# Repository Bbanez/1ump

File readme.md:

# Overview #

1ump is a project started with a goal to develope software and hardware tools needed to create fast, simple and reliable communication networks with focus on embedded devices. The advantage of 1ump solution and CLIN communication protocol, that will be developed in the scope of this projects, is that it will be Open Source, easy and cheap to implement.

## Milestones ##

- Design and test CLIN interface.
- Design child interface schematic.
- Design parent interface schematic.
- Design and test prototype boards.
- Push revision 1 boards.
- Write API for Arduino, Mbed, AVR and STM platforms.
- Write desktop application for network monitoring and control.

## Custom communication protocol ##

This project will use custom communication protocol called CLIN Protocol (for short CLIN) that is developed in the scope of this project. The goal of CLIN is to allow simple and easy-to-use communication protocol for connecting virtually infinite number of devices with few hardware wires as possible while allowing fast and reliable data transfer. Since UART is widely used, it is supported by majority of MCUs and it can be easily converted to USB protocol, therefore CLIN is based on it. CLIN uses some software and hardware implementations on top of UART to allow data transfer between devices connected to communication bus (in CLIN network).

## Abstract ##

UART is a simple protocol that uses only 2 wires for communication, one is TX (transmit line) and other is RX (receive line). To establish communication between two devices over UART, TX line of one device is connected to RX line of other and vice versa, as shown in Figure 1. If there is more then 2 devices that need to be connected together, there is only one way to connect them over UART with out introducing additional components and that is daisy-chaining devices as shown in Figure 2. This is not a major problem if 3 to 4 devices are in network, big problem arise when there are even more devices in the network. By using daisy-chain, if the first device needs to communicate with last device in the chain, communication packet first needs to pass thru all devices in between them. This is time consuming and can not be implemented in real-time systems, on top of that all devices in middle of the chain need to have 2 UARTs and handle packets that are not for them.  

_Figure 1 - Connecting 2 devices over UART._

_Figure 2 - Connecting more then 2 devices over UART using daisy-chain configuration._

As it can be concluded, this is not very practical, therefore daisy-chain can not be main solution. I2C and SPI will not be considered because I2C is limited to 127 devices in network and SPI uses to many cables and both of them can not be easily converted into USB protocol.

To connect more then 2 devices over UART, interface needs to be implemented as shown in Figure 3. Interface block is the hardware level block which purpose is to allow all devices connected together to pull down RX line of master device. In this configuration slave-to-slave communication can not be achieved. Communication packet will first be transmitted to master device and then be broadcasted to all slave devices in network. This solution has one major problem, since all slave devices are connected to the same lines, 2 or more slave devices can start transmitting at the same time. This will result in error on the master side because data will not have valid format. For this to be solved 1 more wire is included in network that is called BUSY line as shown in Figure 4. This line is used to check if communication bus is free for transmission. For example, every time before slave device transmit data to master, it will check BUSY line. If the line is free (not set) that means that bus is free and that packet can be transmitted. Before transmitting packet, slave device will set BUSY line telling all other slave devices that bus is not free for transmission. This will not completely remove simultaneous transmission that more devices but it will minimize it to insignificant level. 

_Figure 3 - Basic idea for connecting more then 2 devices over 1 UART. Basic TWCL network._

_Figure 4 - Full TWCL network._

## TWCL Network configurations ##

TWCL communication is based on master/slave relationship between devices. There are 2 types of bus lines, master bus and slave bus. There can be many configuration but the typical configuration is to have one master bus that have one master device and many slave-master devices connected to it, while slave-master devices has there own slave bus. This configuration is shown in Figure 4.

In same slave bus, direct slave-to-slave communication can not be achieved, instead slave will send packet to master and master will redirect it to selected slave. In time sensitive application this packet propagation time needs to be considered and it is based on communication speed and master redirect time. For slave-to-slave communication between to different bus lines, propagation time is even longer and is depending on number of redirects. For example (follow the Figure 4), if SLAVE 11 want to send packet to SLAVE 02, packet will first go to SLAVE1/MASTER, then it will be redirected to MASTER and then it will be redirected to SLAVE 02. In this way packet needs to go thru 2 redirect stages. Packet that is sent by master device is always broadcasted with the address of the device that is sending the packet and address of the device where packet needs to go. This means that all slave devices in the bus will receive packet sent by master but only the device with good packet address will process it. Same is applicable to slave-master bus line.

- Basic network configuration shown in figure 3.
- Full or extended network configuration shown in figure 4.
- Nested network configuration shown in figure 5.
- Combined network.

_Figure 5 - Nested TWCL network configuration._

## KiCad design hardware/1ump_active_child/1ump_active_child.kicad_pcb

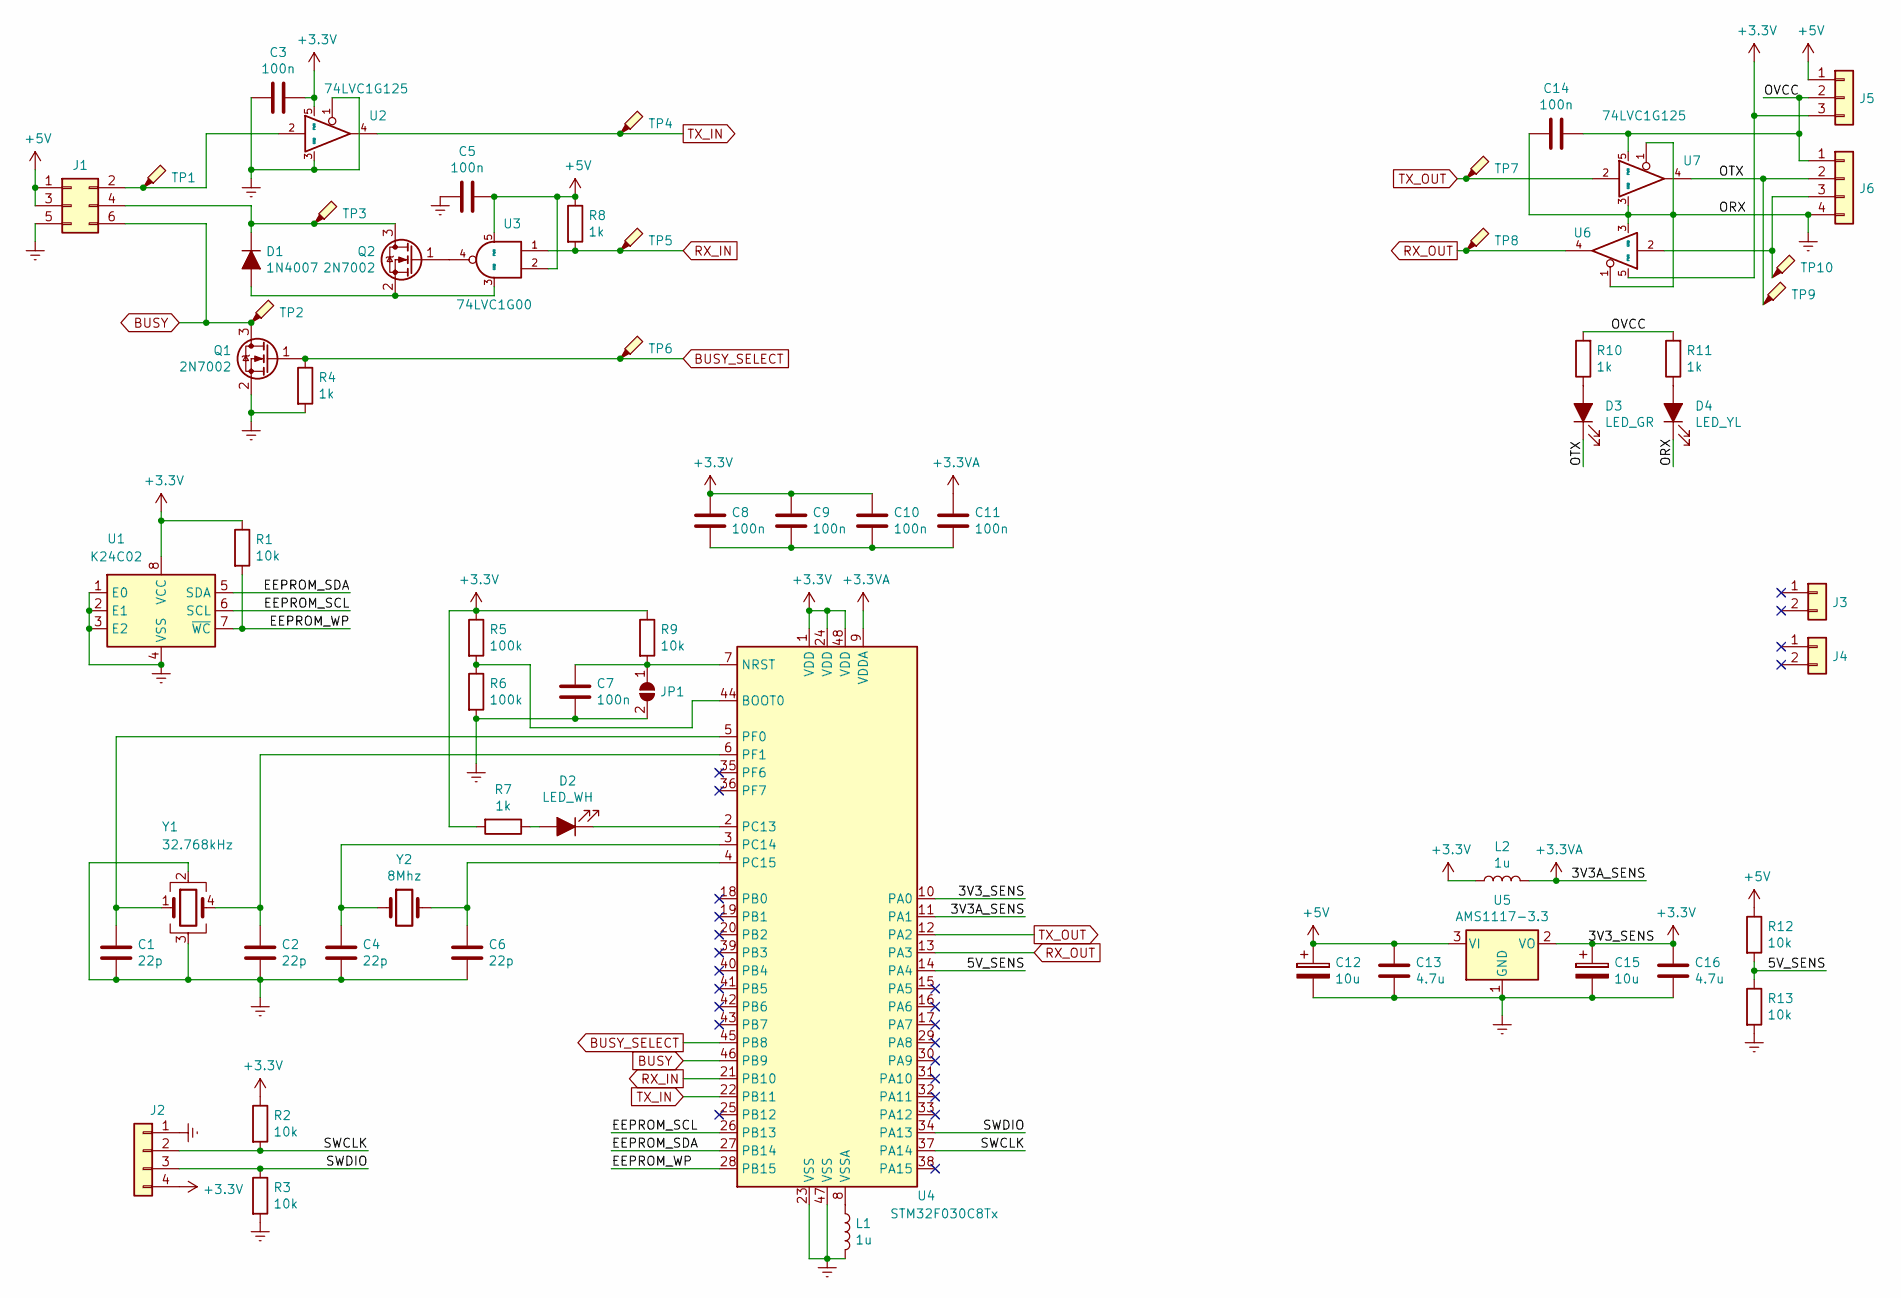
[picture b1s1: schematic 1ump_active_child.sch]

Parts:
C1, C2, C4, C6: 22p; C_0805_2012Metric; LCSC Part C1804
C3, C5, C7, C8, C9, C10, C11, C14: 100n; C_0805_2012Metric; LCSC Part C1804
C12, C15: 10u; CP_Elec_4x4.5
C13, C16: 4.7u; C_0805_2012Metric; LCSC Part C1804
D1: 1N4007; D_0805_2012Metric
D2: LED_WH; LED_0805_2012Metric
D3: LED_GR; LED_0805_2012Metric
D4: LED_YL; LED_0805_2012Metric
J1: Conn_02x03_Odd_Even; PinHeader_2x03_P1.27mm_Vertical
J2, J6: Conn_01x04; JST_PH_S4B-PH-K_1x04_P2.00mm_Horizontal
J3, J4: Conn_01x02; PinHeader_1x02_P1.27mm_Vertical
J5: Conn_01x03; PinHeader_1x03_P2.54mm_Horizontal
JP1: SolderJumper_2_Open; SolderJumper-2_P1.3mm_Open_TrianglePad1.0x1.5mm
L1, L2: 1u; L_0805_2012Metric
Q1, Q2: 2N7002; SOT-23
R1, R2, R3, R9, R12, R13: 10k; R_0805_2012Metric
R4, R7, R8, R10, R11: 1k; R_0805_2012Metric
R5, R6: 100k; R_0805_2012Metric
TP1, TP2, TP3, TP4, TP5, TP6, TP7, TP8, TP9, TP10: TestPoint_Probe; TestPoint_Pad_D1.0mm
U1: K24C02; SOIC-8_3.9x4.9mm_P1.27mm; LCSC Part C83782
U2, U6, U7: 74LVC1G125; SOT-353_SC-70-5
U3: 74LVC1G00; SOT-353_SC-70-5
U4: STM32F030C8Tx; LQFP-48_7x7mm_P0.5mm; LCSC part C23922
U5: AMS1117-3.3; SOT-223-3_TabPin2
Y1: 32.768kHz; Crystal_SMD_SeikoEpson_MC306-4Pin_8.0x3.2mm; LCSC Part C12675
Y2: 8Mhz; Crystal_SMD_HC49-SD; LCSC Part C259041

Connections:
+3.3VA: C11.1, L2.2, U4.9 (VDDA), U4.11 (PA1)
+3V3: C3.2, C8.1, C9.1, C10.1, C15.1, C16.1, J2.4, J5.3, L2.1, R1.1, R2.1, R5.1, R7.2, R9.1, U1.8 (VCC), U2.5 (PWR), U4.1 (VDD), U4.10 (PA0), U4.24 (VDD), U4.48 (VDD), U5.2 (VO), U6.5 (PWR)
+5V: C5.2, C12.1, C13.1, J1.1, J1.3, J5.1, R8.1, R12.1, U3.2, U3.5 (PWR), U5.3 (VI)
/5V_SENS: R12.2, R13.1, U4.14 (PA4)
/EEPROM_SCL: U1.6 (SCL), U4.26 (PB13)
/EEPROM_SDA: U1.5 (SDA), U4.27 (PB14)
/EEPROM_WP: R1.2, U1.7 (~WC), U4.28 (PB15)
/OTX: D3.1 (K), J6.2, TP9.1, U7.4
/OVCC: C14.1, J5.2, J6.1, R10.2, R11.2, U7.5 (PWR)
/SWCLK: J2.2, R2.2, U4.37 (PA14)
/SWDIO: J2.3, R3.1, U4.34 (PA13)
BUSY: J1.6, Q1.3 (D), TP2.1, U4.46 (PB9)
BUSY_SELECT: Q1.1 (G), R4.1, TP6.1, U4.45 (PB8)
Earth: C1.2, C2.2, C3.1, C4.2, C5.1, C6.2, C7.1, C12.2, C13.2, C14.2, C15.2, C16.2, D4.1 (K), J1.5, J2.1, J6.4, JP1.2 (B), L1.2, Q1.2 (S), R3.2, R4.2, R6.2, R13.2, U1.1 (E0), U1.2 (E1), U1.3 (E2), U1.4 (VSS), U2.1, U2.3 (GND), U4.23 (VSS), U4.47 (VSS), U5.1 (GND), U6.1, U6.3 (GND), U7.1, U7.3 (GND), Y1.2, Y1.3
unnamed: C1.1, U4.5 (PF0), Y1.1
unnamed: C2.1, U4.6 (PF1), Y1.4
unnamed: C4.1, U4.3 (PC14), Y2.1
unnamed: C6.1, U4.4 (PC15), Y2.2
unnamed: C7.2, JP1.1 (A), R9.2, U4.7 (NRST)
unnamed: C8.2, C9.2, C10.2, C11.2
unnamed: D1.1 (K), J1.4, Q2.3 (D), TP3.1
unnamed: D1.2 (A), Q2.2 (S), U3.3 (GND)
unnamed: D2.1 (K), U4.2 (PC13)
unnamed: D2.2 (A), R7.1
unnamed: D3.2 (A), R10.1
unnamed: D4.2 (A), R11.1
unnamed: J1.2, TP1.1, U2.2
unnamed: J6.3, TP10.1, U6.2
unnamed: L1.1, U4.8 (VSSA)
unnamed: Q2.1 (G), U3.4
unnamed: R5.2, R6.1, U4.44 (BOOT0)
RX_IN: R8.2, TP5.1, U3.1, U4.21 (PB10)
RX_OUT: TP8.1, U4.13 (PA3), U6.4
TX_IN: TP4.1, U2.4, U4.22 (PB11)
TX_OUT: TP7.1, U4.12 (PA2), U7.2

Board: 2 copper layers, 63 parts (0 on the bottom side), 35 nets, no tracks yet.

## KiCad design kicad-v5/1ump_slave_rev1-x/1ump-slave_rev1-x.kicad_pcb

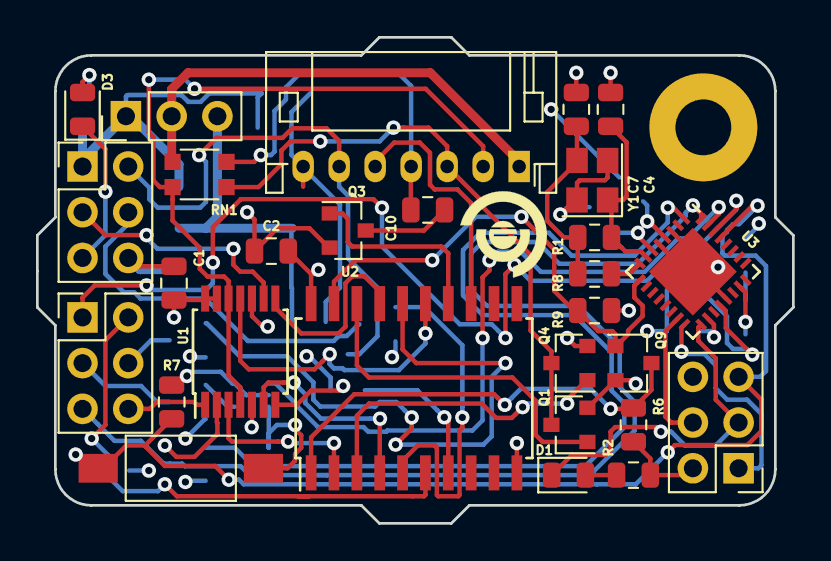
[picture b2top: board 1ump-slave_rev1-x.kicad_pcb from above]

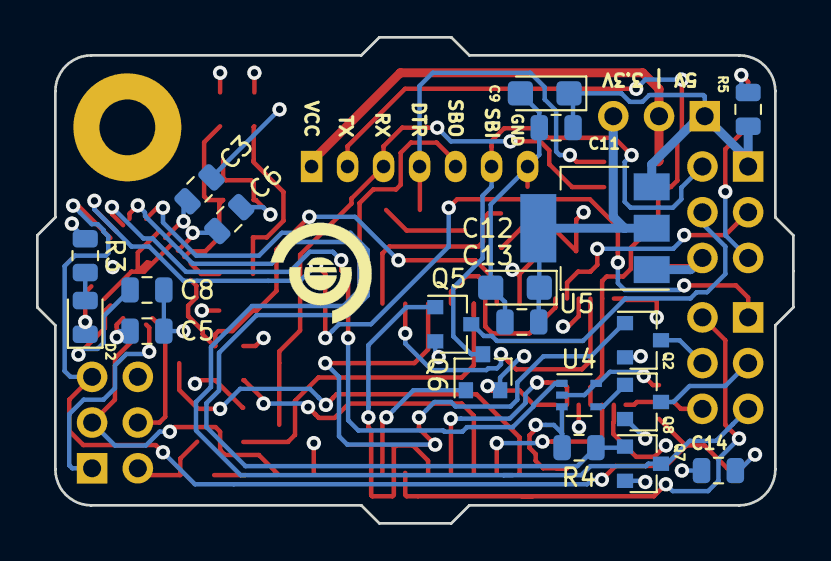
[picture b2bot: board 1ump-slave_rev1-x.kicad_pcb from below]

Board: 4 copper layers, 42.0 x 27.0 mm, 48 parts (20 on the bottom side), 45 nets.

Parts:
C1, C2, C3, C5, C6, C8, C10, C14: 100n; C_0805_2012Metric
C4, C7: 15pF; C_0805_2012Metric
C9, C12: 10u; CP_EIA-3216-12_Kemet-S
C11, C13: 4.7u; C_0805_2012Metric
D1, D2, D3: LED_ALT; LED_0805_2012Metric
J1, J2, J5: Conn_02x03_Odd_Even; PinHeader_2x03_P2.54mm_Vertical
J3: Conn_01x03; PinHeader_1x03_P2.54mm_Vertical
J4: Conn_01x07; JST_PH_S7B-PH-K_1x07_P2.00mm_Horizontal
Q1, Q2, Q3, Q4, Q5, Q6, Q7, Q8, Q9: 2N7002; SOT-23
R1: 1M; R_0805_2012Metric
R2, R3, R5: 1k; R_0805_2012Metric
R4, R6, R7, R9: 10k; R_0805_2012Metric
R8: 0R; R_0805_2012Metric
RN1: 1k; R_Array_Convex_2x1206
SW1: SW_Push; SW_SPST_FSMSM
U1: 74LS00; TSSOP-14_4.4x5mm_P0.65mm
U2: 74HC244; SOIC-20W_7.5x12.8mm_P1.27mm
U3: ATmega328P-MU; QFN-32-1EP_5x5mm_P0.5mm_EP3.45x3.45mm
U4: 74LVC1G00; SOT-353_SC-70-5
U5: AMS1117-3.3; SOT-223-3_TabPin2
Y1: 16MHz_Crystal_GND24; Crystal_SMD_3225-4Pin_3.2x2.5mm

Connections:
+3V3: C12.1, C13.1, J3.3, U5.2
+5V: C1.2, C2.2, C3.1, C5.1, C6.1, C9.1, C11.1, J1.1, J3.1, J5.2, R2.1, R3.1, R5.1, R6.1, R7.1, U1.2, U1.5, U1.10, U1.13, U1.14, U2.20, U3.4, U3.6, U3.18, U4.2, U4.5, U5.3
/BUSY: J2.5, Q7.3, U3.32
/BUSY-SEL: Q7.1, R4.1, U3.1
/CBUS-B: J1.2, J4.6, Q6.3
/CBUS-RX: J1.4, Q5.3
/CBUS-TX: J1.3, U1.9
/CS: Q9.1, R9.1, U2.19, U3.9
/FBUS-DTR: J2.2, U2.6
/FBUS-RX: J2.4, Q2.3
/FBUS-TX: J2.6, U1.1
/MCU-DTR: C10.2, Q3.3
/MCU-RX: J4.3, Q1.3, Q4.3, RN1.3
/MCU-SBO: J4.5, U2.13
/MCU-TX: J4.2, RN1.2, U1.4, U1.12
/MIS: J2.3, Q8.3
/MISO: J5.1, U3.16
/MOS: J2.1, U3.30
/MOSI: J5.4, U3.15
/NCS: Q9.3, R6.2, U2.1
/RST: C14.1, J5.5, R7.2, SW1.1, U3.29
/SCK: D1.1, J5.3, U3.17
/XTAL1: C4.1, R1.2, U3.7, Y1.1
/XTAL2: R8.2, U3.8
Earth: C1.1, C2.1, C3.2, C4.2, C5.2, C6.2, C7.2, C8.2, C9.2, C11.2, C12.2, C13.2, C14.2, D3.1, J1.5, J1.6, J4.7, J5.6, Q1.2, Q2.2, Q3.2, Q4.2, Q5.2, Q6.2, Q7.2, Q8.2, Q9.2, R4.2, R9.2, SW1.2, U1.7, U2.10, U3.3, U3.5, U3.21, U3.33, U4.3, U5.1, Y1.2, Y1.4
unnamed: C7.1, R1.1, R8.1, Y1.3
unnamed: C8.1, U3.20
unnamed: C10.1, J4.4, RN1.4
unnamed: D1.2, R2.2
unnamed: D2.1, U3.23
unnamed: D2.2, R3.2
unnamed: D3.2, R5.2
unnamed: Q1.1, U2.18
unnamed: Q2.1, U2.16
unnamed: Q3.1, U2.14
unnamed: Q4.1, U2.3
unnamed: Q5.1, U2.5
unnamed: Q6.1, U2.7
unnamed: Q8.1, U4.4
unnamed: U1.3, U2.2
unnamed: U1.6, U2.4
unnamed: U1.8, U2.17
unnamed: U1.11, U2.15
unnamed: U3.31, U4.1
VCOM: J3.2, J4.1, RN1.1

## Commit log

2018-06-06 Test
2018-06-06 In progress...
2018-06-06 Creating...
2018-06-07 Added MCU ATtiny44A, LCD driver not done.
2018-06-09 Slave board complit.
2018-06-09 Add MCU to master board.
2018-06-09 Add STM32f103C8T6 and FT232RQ.
2018-06-17 Add master circuit.
2018-07-04 Add changes to slave board.
2018-07-28 Readme in progress...
2018-08-28 Project changes.
2018-08-28 Readme edit.
2018-09-03 TWCL code writing and tesing for java and cpp.
2018-09-04 TWCL code development.
2018-09-11 Add TWCL testing.
2019-01-11 Major structure change.
